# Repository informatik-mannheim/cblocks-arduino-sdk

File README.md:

# cblocks Arduino SDK
Arduino SDK for [cBlocks](https://github.com/informatik-mannheim/cblocks).

## Installation

Example platformio.ini

```
[env:feather]
platform = espressif32
framework = arduino
board = featheresp32

lib_deps =
  https://github.com/informatik-mannheim/cblocks-arduino-sdk
```

## Usage

See example.

cBlocks was developed as part of the ProFI research project (FKZ: 01IS16015) funded by the German Federal Ministry of Education and Research (BMBF).

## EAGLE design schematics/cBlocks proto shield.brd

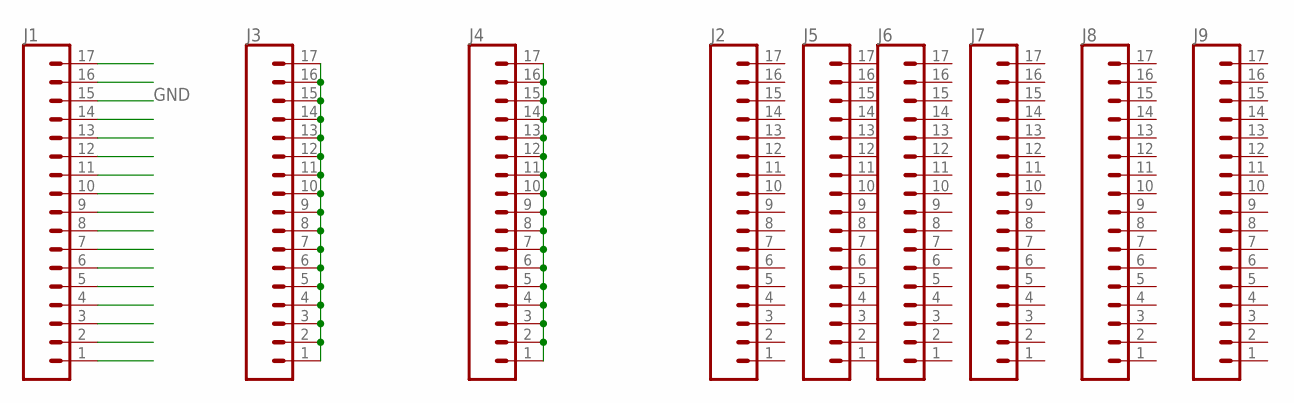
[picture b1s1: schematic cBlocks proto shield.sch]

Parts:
J1, J2, J3, J4, J5, J6, J7, J8, J9: CONN_17NOSILK; 1X17_NO_SILK

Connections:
GND: J1.15
unnamed: J3.1, J3.2, J3.3, J3.4, J3.5, J3.6, J3.7, J3.8, J3.9, J3.10, J3.11, J3.12, J3.13, J3.14, J3.15, J3.16, J3.17
unnamed: J4.1, J4.2, J4.3, J4.4, J4.5, J4.6, J4.7, J4.8, J4.9, J4.10, J4.11, J4.12, J4.13, J4.14, J4.15, J4.16, J4.17
TEST: J1.1

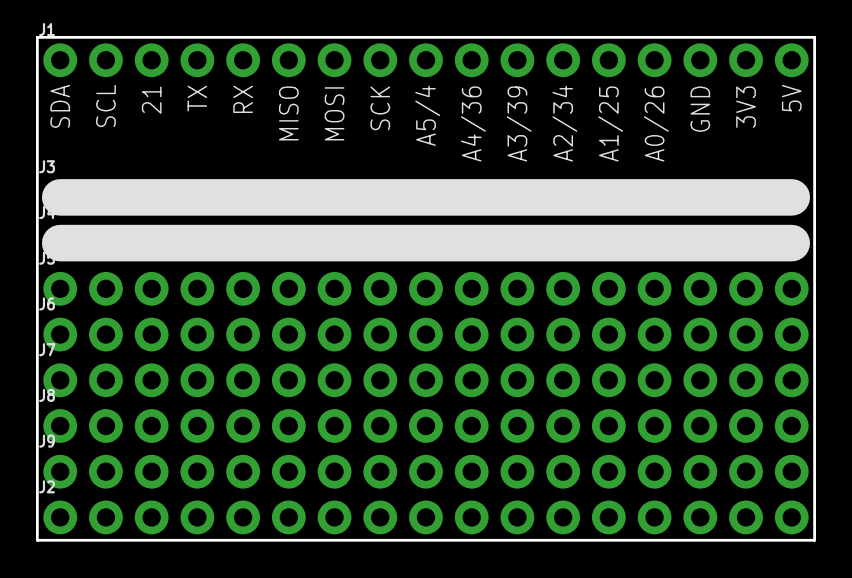
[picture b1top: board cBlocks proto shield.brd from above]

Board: 2 copper layers, 43.2 x 27.9 mm, 9 parts (0 on the bottom side), 2 nets.

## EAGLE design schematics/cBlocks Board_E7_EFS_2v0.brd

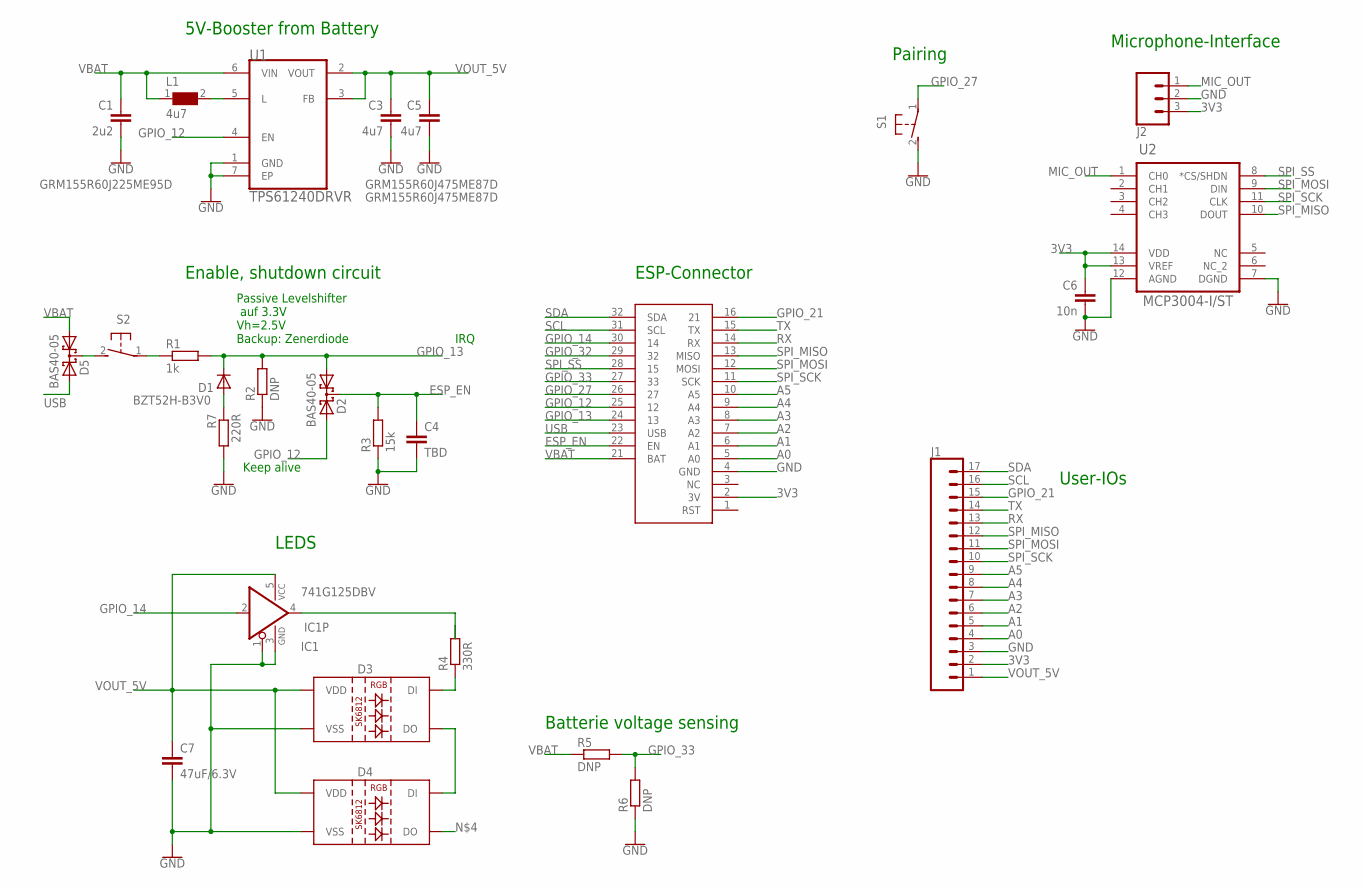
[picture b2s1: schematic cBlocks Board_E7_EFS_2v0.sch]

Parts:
C1: 2u2; C0402K
C3, C5: 4u7; C0402K
C4: TBD; C0805
C6: 10n; C0805
C7: 47uF/6.3V; C1206K
D1: BZT52H-B3V0; SOD123
D2, D5: BAS40-05; SOT23
D3, D4: SK2812SIDE
IC1: 741G125DBV; SOT353
IC2: FEATHERESP32
J1: CONN_17; 1X17
J2: CONN_03; 1X03
L1: 4u7; WE-PMI_0806
R1: 1k; R0805
R2, R5, R6: DNP; R0805
R3: 15k; R0805
R4: 330R; R0805
R7: 220R; R0805
S1, S2: 31-XX; B3F-31XX; MPN B3F-3120
U1: TPS61240DRVR; SON65P200X200X80-7N
U2: MCP3004-I/ST; SO14

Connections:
3V3: C6.1, IC2.2 (3V), J1.2, J2.3, U2.13 (VREF), U2.14 (VDD)
A0: IC2.5 (A0), J1.4
A1: IC2.6 (A1), J1.5
A2: IC2.7 (A2), J1.6
A3: IC2.8 (A3), J1.7
A4: IC2.9 (A4), J1.8
A5: IC2.10 (A5), J1.9
ESP_EN: C4.1, D2.3 (C), IC2.22 (EN), R3.2
GND: C1.2, C3.2, C4.2, C5.2, C6.2, C7.2, D3.4 (VSS), D4.4 (VSS), IC1.1 (OE), IC1.3 (GND), IC2.4 (GND), J1.3, J2.2, R2.1, R3.1, R6.1, R7.2, S1.2 (S), U1.1 (GND), U1.7 (EP), U2.7 (DGND), U2.12 (AGND)
GPIO_12: D2.2 (A2), IC2.25 (12), U1.4 (EN)
GPIO_13: D1.C, D2.1 (A1), IC2.24 (13), R1.2, R2.2
GPIO_14: IC1.2 (I), IC2.30 (14)
GPIO_21: IC2.16 (21), J1.15
GPIO_27: IC2.26 (27), S1.1
GPIO_32: IC2.29 (32)
GPIO_33: IC2.27 (33), R5.2, R6.2
MIC_OUT: J2.1, U2.1 (CH0)
unnamed: D1.A, R7.1
unnamed: L1.2, U1.5 (L)
unnamed: D3.1 (DI), R4.1
unnamed: R1.1, S2.1
unnamed: D3.3 (DO), D4.1 (DI)
unnamed: IC1.4 (O), R4.2
unnamed: D5.3 (C), S2.2 (S)
RX: IC2.14 (RX), J1.13
SCL: IC2.31 (SCL), J1.16
SDA: IC2.32 (SDA), J1.17
SPI_MISO: IC2.13 (MISO), J1.12, U2.10 (DOUT)
SPI_MOSI: IC2.12 (MOSI), J1.11, U2.9 (DIN)
SPI_SCK: IC2.11 (SCK), J1.10, U2.11 (CLK)
SPI_SS: IC2.28 (15), U2.8 (*CS/SHDN)
TX: IC2.15 (TX), J1.14
USB: D5.2 (A2), IC2.23 (USB)
VBAT: C1.1, D5.1 (A1), IC2.21 (BAT), L1.1, R5.1, U1.6 (VIN)
VOUT_5V: C3.1, C5.1, C7.1, D3.2 (VDD), D4.2 (VDD), IC1.5 (VCC), J1.1, U1.2 (VOUT), U1.3 (FB)

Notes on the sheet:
Passive Levelshifter auf 3.3V Vh=2.5V Backup: Zenerdiode
IRQ
Keep alive
Enable, shutdown circuit
Pairing
Batterie voltage sensing
LEDS
Microphone-Interface
ESP-Connector
User-IOs
5V-Booster from Battery

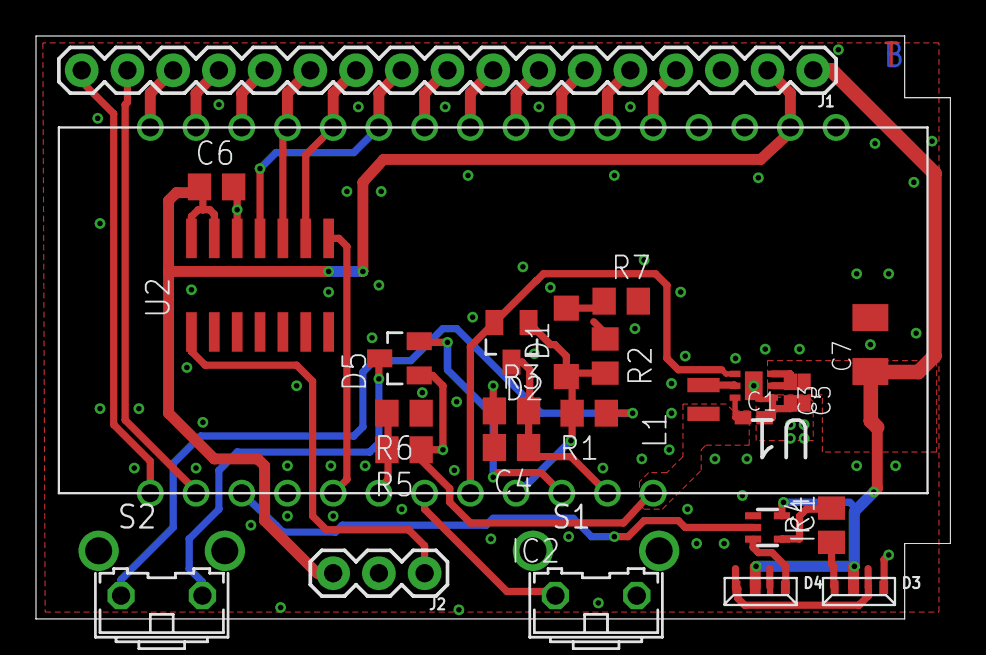
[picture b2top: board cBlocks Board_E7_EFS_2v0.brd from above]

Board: 2 copper layers, 50.8 x 32.4 mm, 27 parts (0 on the bottom side), 34 nets.

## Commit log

2018-02-15 first version with unit tests ready to go
2018-02-15 refactor test structure
2018-02-15 refactor
2018-02-15 first working version with publish
2018-02-16 use arduino strings instead of c-style strings
2018-02-16 first and last will
2018-02-16 first working version of temp sensor
2018-02-19 move delay to main
2018-02-19 add network class
2018-02-19 add maker
2018-02-20 command json validation
2018-02-21 Request/Response-Modell
2018-02-21 callback impl in integration test
2018-02-22 refactor command handling
2018-02-23 switch neopixel on and off
2018-02-23 color json validatoin
2018-02-26 set color
2018-03-12 remove json validation from neopixel
2018-03-26 rfid example init
2018-03-29 first verion of RFID
2018-04-03 rfid working
2018-04-03 heartbeat for neopixel
2018-04-05 room sensor (temp and humidity)
2018-04-06 neopixel with status led
2018-04-06 start neopixel right away
2018-04-12 case plans neopixel
2018-04-12 switch status led pins
2018-04-13 new casings and less power on status led
2018-04-16 fix offline bug for room sensor
2018-04-16 refactor rfid
2018-04-18 buzzer
2018-04-19 introducte update timer
2018-04-19 FIX: boolean
2018-04-19 dont delay in room sensor
2018-04-24 mqtt local
2018-04-26 addressable status led neo pixel
2018-04-27 set status led to index 1
2018-07-11 basic pairing for neopixel Rest to come
2018-07-16 basic power management for esp32
2018-07-16 publish battery status
2018-07-17 restructure directories
2018-07-18 first working pairing version: ugly code to be refactored
2018-07-19 use FSM lib for states
2018-07-19 move neopixel32 to neopixel
2018-07-19 remove astromac
2018-07-19 astromac as submodule
2018-07-19 astramac as submodule
2018-07-19 changed threshold
2018-07-19 changed timeout for wifi connect
2018-07-24 resubsribe to commands
2018-09-05 add usb power manager that basically does nothing
2018-09-05 add tare functionality for scale
2018-11-06 samples updated
2018-11-08 old power management
2018-11-08 clear all pixels on start
2018-11-08 change neopixel coloring scheme
2019-01-16 remove accidental grep file
2019-01-16 redesing pins and graceful shutdown
2019-01-16 refactor: shutdown interrupt only flags that it has been pressed
2019-01-17 button first version
2019-01-23 Button with redesign working
2019-01-23 change debounce time
2019-02-06 Button cblock
2019-02-12 make it pio lib
2019-02-12 astro mech as git dep
2019-02-14 let IRQ pin float
2019-02-19 fix adc
2019-03-05 schematics
2019-03-14 ensure connected

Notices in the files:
parts and their libraries:
SparkFun-Connectors: Licensing: Creative Commons ShareAlike 4.0 International - https://creativecommons.org/licenses/by-sa/4.0
